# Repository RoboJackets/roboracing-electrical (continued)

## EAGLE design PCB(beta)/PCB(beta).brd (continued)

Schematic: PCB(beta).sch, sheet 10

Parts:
C82: 47pF; 0603
C83: 1.0uF; 0603
C87, C88: 0.1uF; 0603
C89: 10uF; 0603
FB4, FB5: 120Ω/1.3A; 0603
J9: DM3AT-SF-PEJM5
R88, R89, R91: 0; 0603
R90: 100k; 0603
U$27: IP4856CX25; 25-WLCSP
U$34: LXES15AAA1-100_ESD_SUPPRESSOR; 0402

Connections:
+1.8V: FB5.1; also elsewhere on the board
+3V3: FB4.1; also elsewhere on the board
+V1P8V_MICROSD: C87.1, FB5.2, U$27.B3 (VCCA)
+V3P3V_MICROSD: C88.1, C89.1, FB4.2, J9.4 (VCC), U$27.A4 (VSUPPLY), U$27.C4 (VSD_REF), U$34.1
+VLDO_SDCARD: C83.1, U$27.B4 (VLDO)
CHS_GND: U$34.2; also elsewhere on the board
GND: C82.2, C83.2, C87.2, C88.2, C89.2, J9.6 (GND), J9.B, J9.MOUNT0 (GND), J9.MOUNT1 (GND), J9.MOUNT2 (GND), J9.MOUNT3 (GND), R90.1, U$27.C3 (GND); also elsewhere on the board
SDCARD_CD_N: R89.1; also elsewhere on the board
SDCARD_CD_N_CONN: J9.A, R89.2, U$27.D3 (CD)
SDCARD_CLK: U$27.C1 (CLK_IN); also elsewhere on the board
SDCARD_CLK_CONN: C82.1, J9.5 (CLK), R91.2
SDCARD_CLK_CONN_R: R91.1, U$27.C5 (CLK_SD)
SDCARD_CMD: U$27.D2 (CMD_H); also elsewhere on the board
SDCARD_CMD_CONN: J9.3 (CMD/MOSI), U$27.D4 (CMD_SD)
SDCARD_D0: U$27.D1 (DATA0_H); also elsewhere on the board
SDCARD_D0_CONN: J9.7 (DATA0/MISO), U$27.D5 (DATA0_SD)
SDCARD_D1: U$27.E1 (DATA1_H); also elsewhere on the board
SDCARD_D1_CONN: J9.8 (DATA1/RSV), U$27.E5 (DATA1_SD)
SDCARD_D2: U$27.A1 (DATA2_H); also elsewhere on the board
SDCARD_D2_CONN: J9.1 (DATA2/NC), U$27.A5 (DATA2_SD)
SDCARD_D3: U$27.B1 (DATA3_H); also elsewhere on the board
SDCARD_D3_CONN: J9.2 (DATA3-CD/CS_N), U$27.B5 (DATA3_SD)
SDCARD_LVL_CLK_FB: U$27.E2 (CLK_FB); also elsewhere on the board
SDCARD_LVL_CMD_DIR: U$27.A2 (DIR_CMD); also elsewhere on the board
SDCARD_LVL_DAT_DIR: U$27.A3 (DIR_0), U$27.E3 (DIR_1_3)
SDCARD_LVL_SEL: U$27.B2 (SEL); also elsewhere on the board
SDCARD_PWR_DOWN_N: R88.1, R90.2; also elsewhere on the board
SDCARD_PWR_DOWN_N_R: R88.2, U$27.C2 (ENABLE)

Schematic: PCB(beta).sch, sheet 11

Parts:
C31, C32, C33, C34, C35, C36, C37, C38, C100, C101, C102: 0.1uF; 0603
C103, C104: 1.0uF; 0603
R92: 1.1k; 0603
R93, R109, R110, R111, R112, R113, R114, R115, R119, R120: 10k; 0603
R94: 100k; 0603
R116: 4.99k; 0603
R117, R118: 2.7k; 0603
U$28: SSM3K56CTL3FCT-ND_NCHAN_MOSFET; 3-XFDFN
U$54: PS8203TQFN32GTR-A3; TQFN32

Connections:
+1.8V: C102.1, C104.1, R92.2, R93.2, R117.2, R118.2, U$54.30 (VDDIO); also elsewhere on the board
+3V3: C101.1, C103.1, R109.2, R110.2, R113.2, R114.2, R119.2, U$54.11 (VDD); also elsewhere on the board
DCIN_EN: R109.1, R111.2, U$54.8 (DCIN_EN)
DDI1_CTRL_CLK: R118.1, U$54.31 (SCL_SRC); also elsewhere on the board
DDI1_CTRL_DAT: R117.1, U$54.32 (SDA_SRC); also elsewhere on the board
EQ: R110.1, R112.2, U$54.13 (EQ)
GND: C100.2, C101.2, C102.2, C103.2, C104.2, R94.1, R111.1, R112.1, R115.1, R120.1, U$28.P$2 (S), U$54.14 (GND), U$54.EXP (EPAD); also elsewhere on the board
HDMI_CEXT: C100.1, U$54.17 (CEXT)
HDMI_CLK_C_DN: C32.2, U$54.10 (IN_CKN)
HDMI_CLK_C_DP: C31.2, U$54.9 (IN_CKP)
HDMI_CLK_DN: C32.1; also elsewhere on the board
HDMI_CLK_DP: C31.1; also elsewhere on the board
HDMI_OB_CLK_DN: U$54.18 (OUT_CKN); also elsewhere on the board
HDMI_OB_CLK_DP: U$54.19 (OUT_CKP); also elsewhere on the board
HDMI_OB_DAT0_DN: U$54.21 (OUT_D0N); also elsewhere on the board
HDMI_OB_DAT0_DP: U$54.22 (OUT_D0P)
HDMI_OB_DAT1_DN: U$54.23 (OUT_D1N); also elsewhere on the board
HDMI_OB_DAT1_DP: U$54.24 (OUT_D1P); also elsewhere on the board
HDMI_OB_DAT2_DN: U$54.26 (OUT_D2N); also elsewhere on the board
HDMI_OB_DAT2_DP: U$54.27 (OUT_D2P); also elsewhere on the board
HDMI_OB_HPD_INV: U$54.25 (HPD_SNK)
HDMI_OB_SCL: U$54.28 (SCL_SNK); also elsewhere on the board
HDMI_OB_SDA: U$54.29 (SDA_SNK); also elsewhere on the board
HDMI_PRE: R119.1, R120.2, U$54.15 (PRE)
HDMI_REXT: R116.2, U$54.16 (REXT)
HDMI_TX_0_C_DN: C34.2, U$54.7 (IN_D0N)
HDMI_TX_0_C_DP: C33.2, U$54.6 (IN_D0P)
HDMI_TX_0_DN: C34.1; also elsewhere on the board
HDMI_TX_0_DP: C33.1; also elsewhere on the board
HDMI_TX_1_C_DN: C37.2, U$54.5 (IN_D1N)
HDMI_TX_1_C_DP: C35.2, U$54.4 (IN_D1P)
HDMI_TX_1_DN: C37.1; also elsewhere on the board
HDMI_TX_1_DP: C35.1; also elsewhere on the board
HDMI_TX_2_C_DN: C38.2, U$54.2 (IN_D2N)
HDMI_TX_2_C_DP: C36.2, U$54.1 (IN_D2P)
HDMI_TX_2_DN: C38.1; also elsewhere on the board
HDMI_TX_2_DP: C36.1; also elsewhere on the board
HPD_SRC: R92.1, U$28.P$3 (D); also elsewhere on the board
HPD_SRC_N: R93.1, R94.2, U$28.P$1 (G), U$54.3 (HPD_SRC)
LS_CFG: R114.1, R115.2, U$54.20 (CFG)
LS_PD_N: R113.1, U$54.12 (PD*)

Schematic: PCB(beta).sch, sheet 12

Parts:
C39, C40: 0.1uF; 0603
C41, C42: 0.22uF; 0603
D4, D5, D6: 0.5A/40V/420mV; SOD-323
J5: 685119134923
R22, R23: 2.7k; 0603
U$12, U$13, U$14, U$15: TCE0806G-900-2P-T200; 0302_(0806_METRIC)

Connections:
+5V: C39.1, D4.A, D5.A, D6.A; also elsewhere on the board
+V5P0V_D: C40.1, C41.1, C42.1, D6.C, J5.18 (+5VPOWER)
CHS_GND: U$12.P5_1 (5), U$12.P5_2 (5), U$12.P6_1 (6), U$12.P6_2 (6), U$13.P5_1 (5), U$13.P5_2 (5), U$13.P6_1 (6), U$13.P6_2 (6), U$14.P5_1 (5), U$14.P5_2 (5), U$14.P6_1 (6), U$14.P6_2 (6), U$15.P5_1 (5), U$15.P5_2 (5), U$15.P6_1 (6), U$15.P6_2 (6); also elsewhere on the board
GND: C39.2, C40.2, C41.2, C42.2, J5.2 (TMDSDATA2SHIELD), J5.5 (TMDSDATA1SHIELD), J5.8 (TMDSDATA0SHIELD), J5.11 (TMDSCLOCKSHIELD); also elsewhere on the board
HDMI_CLK_CONN_DN: J5.12 (TMDSCLOCK-), U$13.P2_1 (2), U$13.P2_2 (2), U$13.P2_3 (2)
HDMI_CLK_CONN_DP: J5.10 (TMDSCLOCK+), U$13.P1_1 (1), U$13.P1_2 (1), U$13.P1_3 (1)
HDMI_DAT0_CONN_DN: J5.9 (TMDSDATA0-), U$12.P2_1 (2), U$12.P2_2 (2), U$12.P2_3 (2)
HDMI_DAT0_CONN_DP: J5.7 (TMDSDATA0+), U$12.P1_1 (1), U$12.P1_2 (1), U$12.P1_3 (1)
HDMI_DAT1_CONN_DN: J5.6 (TMDSDATA1-), U$14.P2_1 (2), U$14.P2_2 (2), U$14.P2_3 (2)
HDMI_DAT1_CONN_DP: J5.4 (TMDSDATA1+), U$14.P1_1 (1), U$14.P1_2 (1), U$14.P1_3 (1)
HDMI_DAT2_CONN_DN: J5.3 (TMDSDATA2-), U$15.P2_1 (2), U$15.P2_2 (2), U$15.P2_3 (2)
HDMI_DAT2_CONN_DP: J5.1 (TMDSDATA2+), U$15.P1_1 (1), U$15.P1_2 (1), U$15.P1_3 (1)
HDMI_OB_CLK_DN: U$13.P3_1 (3), U$13.P3_2 (3), U$13.P3_3 (3); also elsewhere on the board
HDMI_OB_CLK_DP: U$13.P4_1 (4), U$13.P4_2 (4), U$13.P4_3 (4); also elsewhere on the board
HDMI_OB_DAT0_DN: U$12.P3_1 (3), U$12.P3_2 (3), U$12.P3_3 (3); also elsewhere on the board
HDMI_OB_DAT1_DN: U$14.P3_1 (3), U$14.P3_2 (3), U$14.P3_3 (3); also elsewhere on the board
HDMI_OB_DAT1_DP: U$14.P4_1 (4), U$14.P4_2 (4), U$14.P4_3 (4); also elsewhere on the board
HDMI_OB_DAT2_DN: U$15.P3_1 (3), U$15.P3_2 (3), U$15.P3_3 (3); also elsewhere on the board
HDMI_OB_DAT2_DP: U$15.P4_1 (4), U$15.P4_2 (4), U$15.P4_3 (4); also elsewhere on the board
HDMI_OB_SCL: J5.15 (SCL), R22.2; also elsewhere on the board
HDMI_OB_SCL_D: D4.C, R22.1
HDMI_OB_SDA: J5.16 (SDA), R23.2; also elsewhere on the board
HDMI_OB_SDA_D: D5.C, R23.1
TP_HDMI_CEC: J5.13 (CEC)

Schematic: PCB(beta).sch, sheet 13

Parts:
C43, C44, C45, C46, C47, C48, C49, C50, C51, C52: 0.1uF; 0603
R24, R29, R30, R39: 200k; 0603
R25, R26, R27, R28, R31, R32, R33, R34, R35, R36, R37, R38: 100k; 0603
U4, U5, U6, U7, U8: LSF0108RKSR; RKS20_1P1X3P1

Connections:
+1.8V: C44.1, C45.1, C47.1, C49.1, C51.1, R25.2, R26.2, R33.2, R34.2, R35.2, R36.2, U4.2 (VREF_A), U5.2 (VREF_A), U6.2 (VREF_A), U7.2 (VREF_A), U8.2 (VREF_A); also elsewhere on the board
+3V3: C50.1, R24.2, R27.2, R28.2, R29.2, R30.2, R31.2, R32.2, R37.2, R38.2, R39.2, U7.19 (VREF_B), U7.20 (EN); also elsewhere on the board
CLK_19P2M: U7.6 (A4); also elsewhere on the board
CLK_19P2M_LS: U7.15 (B4); also elsewhere on the board
CODEC_MCLK: U6.8 (A6); also elsewhere on the board
CODEC_MCLK_LS: U6.13 (B6); also elsewhere on the board
EN6: C52.1, R39.1, U8.19 (VREF_B), U8.20 (EN)
GND: C43.2, C44.2, C45.2, C46.2, C47.2, C48.2, C49.2, C50.2, C51.2, C52.2, U4.1 (GND), U4.21 (EPAD), U5.1 (GND), U5.21 (EPAD), U6.1 (GND), U6.21 (EPAD), U7.1 (GND), U7.21 (EPAD), U8.1 (GND), U8.21 (EPAD); also elsewhere on the board
GPIO_22: U7.3 (A1); also elsewhere on the board
GPIO_22_LS: U7.18 (B1); also elsewhere on the board
I2C_0_SCL: R34.1, U7.8 (A6); also elsewhere on the board
I2C_0_SCL_LS: R31.1, U7.13 (B6); also elsewhere on the board
I2C_0_SDA: R33.1, U7.4 (A2); also elsewhere on the board
I2C_0_SDA_LS: R32.1, U7.17 (B2); also elsewhere on the board
I2S_1_CLK: U6.9 (A7); also elsewhere on the board
I2S_1_CLK_LS: U6.12 (B7); also elsewhere on the board
I2S_1_FS: U6.7 (A5); also elsewhere on the board
I2S_1_FS_LS: U6.14 (B5); also elsewhere on the board
I2S_1_RXD: U6.6 (A4); also elsewhere on the board
I2S_1_RXD_LS: U6.15 (B4); also elsewhere on the board
I2S_1_TXD: U6.5 (A3); also elsewhere on the board
I2S_1_TXD_LS: U6.16 (B3); also elsewhere on the board
ISH_GPIO_0: U8.6 (A4); also elsewhere on the board
ISH_GPIO_0_LS: U8.15 (B4); also elsewhere on the board
ISH_GPIO_1: U8.5 (A3); also elsewhere on the board
ISH_GPIO_1_LS: U8.16 (B3); also elsewhere on the board
ISH_GPIO_2: U4.8 (A6); also elsewhere on the board
ISH_GPIO_2_LS: U4.13 (B6); also elsewhere on the board
ISH_GPIO_3: U4.7 (A5); also elsewhere on the board
ISH_GPIO_3_LS: U4.14 (B5); also elsewhere on the board
ISH_GPIO_4: U8.4 (A2); also elsewhere on the board
ISH_GPIO_4_LS: U8.17 (B2); also elsewhere on the board
ISH_GPIO_5: U4.6 (A4); also elsewhere on the board
ISH_GPIO_5_LS: U4.15 (B4); also elsewhere on the board
ISH_GPIO_6: U8.3 (A1); also elsewhere on the board
ISH_GPIO_6_LS: U8.18 (B1); also elsewhere on the board
ISH_I2C_0_SCL: R25.1, U5.6 (A4); also elsewhere on the board
ISH_I2C_0_SCL_LS: R27.1, U5.15 (B4); also elsewhere on the board
ISH_I2C_0_SDA: R26.1, U5.5 (A3); also elsewhere on the board
ISH_I2C_0_SDA_LS: R28.1, U5.16 (B3); also elsewhere on the board
ISH_I2C_1_SCL: R36.1, U8.8 (A6); also elsewhere on the board
ISH_I2C_1_SCL_LS: R37.1, U8.13 (B6); also elsewhere on the board
ISH_I2C_1_SDA: R35.1, U8.7 (A5); also elsewhere on the board
ISH_I2C_1_SDA_LS: R38.1, U8.14 (B5); also elsewhere on the board
unnamed: C48.1, R30.1, U6.19 (VREF_B), U6.20 (EN)
unnamed: C46.1, R29.1, U5.19 (VREF_B), U5.20 (EN)
unnamed: C43.1, R24.1, U4.19 (VREF_B), U4.20 (EN)
PMIC_PWRGOOD: U6.10 (A8); also elsewhere on the board
PMIC_PWRGOOD_LS: U6.11 (B8); also elsewhere on the board
PMIC_RESET_N: U4.3 (A1); also elsewhere on the board
PMIC_RESET_N_LS: U4.18 (B1); also elsewhere on the board
PWM_0: U4.5 (A3); also elsewhere on the board
PWM_0_LS: U4.16 (B3); also elsewhere on the board
PWM_1: U4.4 (A2); also elsewhere on the board
PWM_1_LS: U4.17 (B2); also elsewhere on the board
PWM_2: U5.4 (A2); also elsewhere on the board
PWM_2_LS: U5.17 (B2); also elsewhere on the board
PWM_3: U5.3 (A1); also elsewhere on the board
PWM_3_LS: U5.18 (B1); also elsewhere on the board
SPI_1_CLK: U6.3 (A1); also elsewhere on the board
SPI_1_CLK_LS: U6.18 (B1); also elsewhere on the board
SPI_1_FS0: U7.10 (A8); also elsewhere on the board
SPI_1_FS0_LS: U7.11 (B8); also elsewhere on the board
SPI_1_FS2: U5.7 (A5); also elsewhere on the board
SPI_1_FS2_LS: U5.14 (B5); also elsewhere on the board
SPI_1_MISO: U7.7 (A5); also elsewhere on the board
SPI_1_MISO_LS: U7.14 (B5); also elsewhere on the board
SPI_1_MOSI: U6.4 (A2); also elsewhere on the board
SPI_1_MOSI_LS: U6.17 (B2); also elsewhere on the board
UART_0_TXD: U7.5 (A3); also elsewhere on the board
UART_0_TXD_LS: U7.16 (B3); also elsewhere on the board
UART_1_RXD: U4.10 (A8); also elsewhere on the board
UART_1_RXD_LS: U4.11 (B8); also elsewhere on the board
UART_1_TXD: U4.9 (A7); also elsewhere on the board
UART_1_TXD_LS: U4.12 (B7); also elsewhere on the board

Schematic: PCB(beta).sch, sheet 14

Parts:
C53, C54, C55, C56: 0.1uF; 0603
D7, D8, D9, D10: GREEN; LED-0603
J6: SSM-120-S-DV; CON40_2X20_DU_SSM
Q1, Q2: TRANS_NPN_DUAL-MBT3904DW1T1; SC70-6
R40, R41, R42, R43: 1.1k; 0603
R44, R45, R46, R47: 560; 2010
U$35, U$36: LXES15AAA1-100_ESD_SUPPRESSOR; 0402

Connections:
+5V: R44.2, R45.2, R46.2, R47.2; also elsewhere on the board
+VDD1: C55.1, C56.1, J6.34, U$35.1; also elsewhere on the board
+VDD3: C53.1, C54.1, J6.40, U$36.1; also elsewhere on the board
CLK_19P2M_LS: J6.5; also elsewhere on the board
CODEC_MCLK_LS: J6.20; also elsewhere on the board
GND: C53.2, C54.2, C55.2, C56.2, J6.36, J6.37, J6.38, J6.39, Q1.1 (E), Q1.4 (E), Q2.1 (E), Q2.4 (E), U$35.2, U$36.2; also elsewhere on the board
GPIO_22_LS: J6.1; also elsewhere on the board
I2C_0_SCL_LS: J6.13; also elsewhere on the board
I2C_0_SDA_LS: J6.11; also elsewhere on the board
I2S_1_CLK_LS: J6.18; also elsewhere on the board
I2S_1_FS_LS: J6.16; also elsewhere on the board
I2S_1_RXD_LS: J6.12; also elsewhere on the board
I2S_1_TXD_LS: J6.14; also elsewhere on the board
ISH_GPIO0_COL: D7.A, R44.1
ISH_GPIO0_COL_D: D7.C, Q1.3 (C)
ISH_GPIO1_COL: D8.A, R45.1
ISH_GPIO1_COL_D: D8.C, Q1.6 (C)
ISH_GPIO2_COL: D9.A, R46.1
ISH_GPIO2_COL_D: D9.C, Q2.3 (C)
ISH_GPIO3_COL: D10.A, R47.1
ISH_GPIO3_COL_D: D10.C, Q2.6 (C)
ISH_GPIO_0: R40.1; also elsewhere on the board
ISH_GPIO_0_LS: J6.35; also elsewhere on the board
ISH_GPIO_0_R: Q1.5 (B), R40.2
ISH_GPIO_1: R41.1; also elsewhere on the board
ISH_GPIO_1_LS: J6.33; also elsewhere on the board
ISH_GPIO_1_R: Q1.2 (B), R41.2
ISH_GPIO_2: R42.1; also elsewhere on the board
ISH_GPIO_2_LS: J6.31; also elsewhere on the board
ISH_GPIO_2_R: Q2.5 (B), R42.2
ISH_GPIO_3: R43.1; also elsewhere on the board
ISH_GPIO_3_LS: J6.29; also elsewhere on the board
ISH_GPIO_3_R: Q2.2 (B), R43.2
ISH_GPIO_4_LS: J6.27; also elsewhere on the board
ISH_GPIO_5_LS: J6.25; also elsewhere on the board
ISH_GPIO_6_LS: J6.23; also elsewhere on the board
ISH_I2C_0_SCL_LS: J6.17; also elsewhere on the board
ISH_I2C_0_SDA_LS: J6.15; also elsewhere on the board
ISH_I2C_1_SCL_LS: J6.21; also elsewhere on the board
ISH_I2C_1_SDA_LS: J6.19; also elsewhere on the board
PMIC_PWRGOOD_LS: J6.9; also elsewhere on the board
PMIC_RESET_N_LS: J6.3; also elsewhere on the board
PWM_0_LS: J6.26; also elsewhere on the board
PWM_1_LS: J6.28; also elsewhere on the board
PWM_2_LS: J6.30; also elsewhere on the board
PWM_3_LS: J6.32; also elsewhere on the board
SPI_1_CLK_LS: J6.10; also elsewhere on the board
SPI_1_FS0_LS: J6.6; also elsewhere on the board
SPI_1_FS2_LS: J6.8; also elsewhere on the board
SPI_1_MISO_LS: J6.2; also elsewhere on the board
SPI_1_MOSI_LS: J6.4; also elsewhere on the board
UART_0_TXD_LS: J6.7; also elsewhere on the board
UART_1_RXD_LS: J6.24; also elsewhere on the board
UART_1_TXD_LS: J6.22; also elsewhere on the board

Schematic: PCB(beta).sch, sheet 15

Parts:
C57, C58, C59, C60, C61, C62, C63, C64, C65, C66, C67, C68, C69, C70: 0.1uF; 0603
J7: SSM-120-S-DV; CON40_2X20_DU_SSM
R48, R49, R50, R51, R52, R53, R58, R59: 100k; 0603
R54, R55, R56, R57: 200k; 0603
U9, U10, U11, U12: LSF0108RKSR; RKS20_1P1X3P1
U$37, U$38, U$39: LXES15AAA1-100_ESD_SUPPRESSOR; 0402

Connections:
+1.8V: C57.1, C59.1, C61.1, C63.1, C65.1, C66.1, J7.12, R48.2, R49.2, R50.2, R58.2, U9.2 (VREF_A), U10.2 (VREF_A), U11.2 (VREF_A), U12.2 (VREF_A), U$37.1; also elsewhere on the board
+3V3: C67.1, C68.1, J7.6, J7.8, R51.2, R52.2, R53.2, R54.2, R55.2, R56.2, R57.2, R59.2, U$38.1; also elsewhere on the board
+5V: C69.1, C70.1, J7.2, J7.4, U$39.1; also elsewhere on the board
AVS_M_CLK_A1: U10.3 (A1); also elsewhere on the board
AVS_M_CLK_A1_LS: J7.26, U10.18 (B1)
AVS_M_CLK_B1: U10.8 (A6); also elsewhere on the board
AVS_M_CLK_B1_LS: J7.24, U10.13 (B6)
AVS_M_DATA_1: U10.9 (A7); also elsewhere on the board
AVS_M_DATA_1_LS: J7.22, U10.12 (B7)
BLDRW_0_PWM: U10.5 (A3); also elsewhere on the board
BLDRW_0_PWM_LS: J7.17, U10.16 (B3)
DISPLAY_0_BIAS_EN: U10.4 (A2); also elsewhere on the board
DISPLAY_0_BIAS_EN_LS: J7.13, U10.17 (B2)
DISPLAY_0_BKLT_EN: U10.6 (A4); also elsewhere on the board
DISPLAY_0_BKLT_EN_LS: J7.15, U10.15 (B4)
DISPLAY_0_RST_N: U10.10 (A8); also elsewhere on the board
DISPLAY_0_RST_N_LS: J7.11, U10.11 (B8)
FLASH_RST_N: U11.4 (A2); also elsewhere on the board
FLASH_RST_N_LS: J7.18, U11.17 (B2)
FLASH_TORCH: U11.5 (A3); also elsewhere on the board
FLASH_TORCH_LS: J7.16, U11.16 (B3)
FLASH_TRIGGER: U11.3 (A1); also elsewhere on the board
FLASH_TRIGGER_LS: J7.20, U11.18 (B1)
GND: C57.2, C58.2, C59.2, C60.2, C61.2, C62.2, C63.2, C64.2, C65.2, C66.2, C67.2, C68.2, C69.2, C70.2, J7.1, J7.3, J7.5, J7.7, J7.9, J7.14, U9.1 (GND), U9.21 (EPAD), U10.1 (GND), U10.21 (EPAD), U11.1 (GND), U11.21 (EPAD), U12.1 (GND), U12.21 (EPAD), U$37.2, U$38.2, U$39.2; also elsewhere on the board
I2C_1_SCL: R48.1, U9.10 (A8); also elsewhere on the board
I2C_1_SCL_LS: J7.33
I2C_1_SDA: R58.1, U12.3 (A1); also elsewhere on the board
I2C_1_SDA_LS: J7.31, R59.1, U12.18 (B1)
I2C_2_SCL: R49.1, U9.8 (A6); also elsewhere on the board
I2C_2_SCL_LS: J7.37, R51.1, U9.13 (B6)
I2C_2_SDA: R50.1, U9.9 (A7); also elsewhere on the board
I2C_2_SDA_LS: J7.35, R52.1, R53.1, U9.11 (B8), U9.12 (B7)
ISH_UART_0_CTS: U9.4 (A2); also elsewhere on the board
ISH_UART_0_CTS_LS: J7.40, U9.17 (B2)
ISH_UART_0_RTS: U9.5 (A3); also elsewhere on the board
ISH_UART_0_RTS_LS: J7.38, U9.16 (B3)
ISH_UART_0_RXD: U9.6 (A4); also elsewhere on the board
ISH_UART_0_RXD_LS: J7.36, U9.15 (B4)
ISH_UART_0_TXD: U9.7 (A5); also elsewhere on the board
ISH_UART_0_TXD_LS: J7.34, U9.14 (B5)
unnamed: C62.1, R56.1, U11.19 (VREF_B), U11.20 (EN)
unnamed: C60.1, R55.1, U10.19 (VREF_B), U10.20 (EN)
unnamed: C64.1, R57.1, U12.19 (VREF_B), U12.20 (EN)
unnamed: C58.1, R54.1, U9.19 (VREF_B), U9.20 (EN)
PMIC_SLPCLK_1: U9.3 (A1); also elsewhere on the board
PMIC_SLPCLK_1_LS: U9.18 (B1)
PMIC_SPLCLK_1_LS: J7.39
SPI_0_CLK: U12.10 (A8); also elsewhere on the board
SPI_0_CLK_LS: J7.25, U12.11 (B8)
SPI_0_FS0: U11.6 (A4); also elsewhere on the board
SPI_0_FS0_LS: J7.19, U11.15 (B4)
SPI_0_FS1: U10.7 (A5); also elsewhere on the board
SPI_0_FS1_LS: J7.21, U10.14 (B5)
SPI_0_FS2: U12.7 (A5); also elsewhere on the board
SPI_0_FS2_LS: J7.23, U12.14 (B5)
SPI_0_MISO: U12.5 (A3); also elsewhere on the board
SPI_0_MISO_LS: J7.29, U12.16 (B3)
SPI_0_MOSI: U12.9 (A7); also elsewhere on the board
SPI_0_MOSI_LS: J7.27, U12.12 (B7)
UART_0_CTS: U12.4 (A2); also elsewhere on the board
UART_0_CTS_LS: J7.32, U12.17 (B2)
UART_0_RTS: U12.8 (A6); also elsewhere on the board
UART_0_RTS_LS: J7.30, U12.13 (B6)
UART_0_RXD: U12.6 (A4); also elsewhere on the board
UART_0_RXD_LS: J7.28, U12.15 (B4); also elsewhere on the board

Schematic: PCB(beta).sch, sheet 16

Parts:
R60: 100k; 0603
R61: 100; 0603
R62, R63: 3.3k; 0603
S1, S2, S3: MOMENTARY-SWITCH-SPST-2-SMD-4.6X2.8MM; TACTILE_SWITCH_SMD_4.6X2.8MM
U$16: TSM-102-01-L-DV-TR; 4X-.145X.05_SQ
U$40, U$41, U$42, U$43, U$44: LXES15AAA1-100_ESD_SUPPRESSOR; 0402

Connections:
+VDD1: R60.2, R61.2; also elsewhere on the board
BTN_N: R60.1, S2.3, S2.4, U$41.1; also elsewhere on the board
GND: R62.1, R63.1, S1.1, S1.2, S2.1, S2.2, U$40.2, U$41.2, U$42.2, U$43.2, U$44.2; also elsewhere on the board
PMIC_PWRBTN_N: S1.3, S1.4, U$42.1; also elsewhere on the board
SPI_1_FS2: U$16.P$3, U$44.1; also elsewhere on the board
SPI_1_FS2_PD: R62.2, U$16.P$4
UART_1_TXD: U$16.P$1, U$43.1; also elsewhere on the board
UART_1_TXD_PD: R63.2, U$16.P$2
UART_2_TXD: S3.1, S3.2, U$40.1; also elsewhere on the board
UART_2_TXD_PU: R61.1, S3.3, S3.4

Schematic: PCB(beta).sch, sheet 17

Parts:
C71, C90: 0.1uF; 0603
H1, H2, H3, H4: MOUNT-PAD-ROUND4.1; 4,1-PAD
J8: CONN_03SMD; 1X03-1MM-RA
R64, R65, R66, R67, R96: 10k; 0603
R68, R69, R70, R71, R72, R73, R74: 0; 0603
R95: 1.1k; 0603
U$17: M24M02-DRMN6TP; SOIC8
U$29: LXES15AAA1-100_ESD_SUPPRESSOR; 0402
U$30: BK-916-TR_12MM_COINCELL; 12MM_COINCELL
U$45, U$46, U$47, U$48: 92320A282_1/8_SPACER; 1/8"RING

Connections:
+3V3: R96.2; also elsewhere on the board
+5V: C90.1, J8.1; also elsewhere on the board
+VDD1: C71.1, R64.2, R66.2, R69.2; also elsewhere on the board
+VRTC: R95.1; also elsewhere on the board
CHS_GND: R71.2, R72.2, R73.2, R74.2; also elsewhere on the board
EEPROM_E2: R66.1, R67.2, U$17.3 (E2)
EEPROM_VCC: R69.1, U$17.8 (VCC)
EEPROM_WC_N: R64.1, R65.2, U$17.7 (/WC)
FAN_CTRL: J8.2, R96.1
GND: C71.2, C90.2, H1.B4,1, H2.B4,1, H3.B4,1, H4.B4,1, J8.3, R65.1, R67.1, R71.1, R72.1, R73.1, R74.1, U$17.4 (VSS), U$29.2, U$30.P$3 (-), U$45.P$1, U$46.P$1, U$47.P$1, U$48.P$1; also elsewhere on the board
I2C_0_SCL: R70.1; also elsewhere on the board
I2C_0_SCL_EE_R: R70.2, U$17.6 (SCL)
I2C_0_SDA: R68.2; also elsewhere on the board
I2C_0_SDA_EE_R: R68.1, U$17.5 (SDA)
unnamed: R95.2, U$29.1, U$30.P$1 (+), U$30.P$2 (+)

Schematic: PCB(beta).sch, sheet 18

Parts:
C130, C131: 22pF; 0603
C132, C133: 0.1uF; 0603
J10: CONN_03X2FEMALE_SMD; 2X3_SMD
Q3, Q4: 220mA/50V/3.5Ω; SOT23-3
R121, R122, R123, R124, R125: 10k; 0603
S4: MOMENTARY-SWITCH-SPST-2-SMD-4.6X2.8MM; TACTILE_SWITCH_SMD_4.6X2.8MM
U13: ATMEGA328P_TQFP; TQFP32-08
Y1: 16MHz; CRYSTAL-SMD-5X3.2-4PAD

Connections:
+3V3: Q3.1 (G), Q4.1 (G), R122.2, R125.2; also elsewhere on the board
+5V: C133.1, J10.2, R121.2, R123.2, R124.2, U13.4 (VCC), U13.6 (VCC), U13.18 (AVCC); also elsewhere on the board
GND: C130.1, C131.1, C132.2, C133.2, J10.6, S4.1, S4.2, U13.3 (GND), U13.5 (GND), U13.21 (AGND); also elsewhere on the board
MICRO_RST: J10.5, R121.1, S4.3, S4.4, U13.29 (PC6(/RESET))
unnamed: J10.4, U13.15 (PB3(MOSI/OC2))
unnamed: J10.1, U13.16 (PB4(MISO))
unnamed: J10.3, U13.17 (PB5(SCK))
unnamed: C130.2, U13.7 (PB6(XTAL1/TOSC1)), Y1.3 (2)
unnamed: C131.2, U13.8 (PB7(XTAL2/TOSC2)), Y1.1
unnamed: Q3.3 (D), R123.1, U13.30 (PD0(RXD))
unnamed: C132.1, U13.20 (AREF)
unnamed: Q4.3 (D), R124.1, U13.31 (PD1(TXD))
UART_0_RXD_LS: Q4.2 (S), R125.1; also elsewhere on the board
UART_0_TXD_LS: Q3.2 (S), R122.1; also elsewhere on the board

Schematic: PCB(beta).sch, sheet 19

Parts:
C134, C135: 18pF; 0603
C136: 1.0uF; 0603
C137, C138, C140, C141, C142, C143, C144, C145, C146, C147, C148, C149, C150, C151, C152, C153, C154, C157, C158, C159, C160, C161, C162, C163, C164, C169, C170, C171, C172, C176, C177, C180, C181, C182, C184: 0.1uF; 0603
C139, C155, C156: 10uF; 0603
C165, C166, C167, C168: 1nF; 0603
C173, C175: 4.7uF; 0603
C174: 10nF; 0603
C178, C179, C183, C185: 150uF; CPOL-RADIAL-2.5MM-6.5MM
FB6, FB7, FB8, FB9, FB10: 30Ω/1.8A; 0603
K2, K3, K4, K5: 692112030100
R126, R138, R139, R140, R141: 1M; 0603
R127, R128, R130, R132, R134, R135, R136, R137: 4.7k; 0603
R129: 9.53k; 0603
R131, R143, R144, R146, R147: 10k; 0603
R133: 90.9k; 0603
R142, R145: 25.5k; 0603
U$57: TUSB8041; QFN64-9X9
U$58: ADP1706ARDZ-1.1-R7; SOIC8
U$59, U$60: TPS2561DRCT; 10-VSON
Y2: 24MHz; CRYSTAL-SMD-5X3.2-4PAD

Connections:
+1V1: C148.1, C149.1, C150.1, C151.1, C152.1, C153.1, C154.1, C155.1, C175.1, U$57.5 (VDD1), U$57.8 (VDD2), U$57.13 (VDD3), U$57.21 (VDD4), U$57.28 (VDD5), U$57.31 (VDD6), U$57.51 (VDD7), U$57.57 (VDD8), U$58.5 (OUT), U$58.6 (OUT2), U$58.7 (SENSE)
+3V3: C173.1, FB6.2, R134.2, R135.2, R136.2, R137.2, R143.2, R144.2, R146.2, R147.2, U$58.1 (EN), U$58.3 (IN), U$58.4 (IN2); also elsewhere on the board
+3V3_HUB: C156.1, C157.1, C158.1, C159.1, C160.1, FB6.1
+5V: C176.1, C177.1, U$59.2_1 (IN), U$59.2_2 (IN), U$59.3_1 (IN2), U$59.3_2 (IN2), U$60.2_1 (IN), U$60.2_2 (IN), U$60.3_1 (IN2), U$60.3_2 (IN2); also elsewhere on the board
DN1_VBUS: C178.1 (+), C180.1, FB7.1, U$59.9_1 (OUT1), U$59.9_2 (OUT1)
DN2_VBUS: C179.1 (+), C181.1, FB8.1, U$59.8_1 (OUT2), U$59.8_2 (OUT2)
DN3_VBUS: C182.1, C183.1 (+), FB9.1, U$60.9_1 (OUT1), U$60.9_2 (OUT1)
DN4_VBUS: FB10.1
GND: C134.1, C135.1, C136.2, C139.2, C156.2, C157.2, C158.2, C159.2, C160.2, C161.2, C162.2, C163.2, C164.2, C165.1, C165.2, C166.1, C166.2, C167.1, C167.2, C168.1, C168.2, C169.1, C169.2, C170.1, C170.2, C171.1, C171.2, C172.1, C172.2, C173.2, C174.2, C175.2, C176.2, C177.2, C178.2 (-), C179.2 (-), C180.2, C181.2, C182.2, C183.2 (-), C184.2, C185.2 (-), K2.4 (GND), K2.7 (GND_DRAIN), K3.4 (GND), K3.7 (GND_DRAIN), K4.4 (GND), K5.4 (GND), R127.1, R128.1, R129.1, R130.1, R131.1, R132.1, R138.1, R138.2, R139.1, R139.2, R140.1, R140.2, R141.1, R141.2, R142.1, R145.1, U$57.16 (VDD33_1), U$57.34 (VDD33_2), U$57.52 (VDD33_3), U$57.63 (VDD33_4), U$57.EXP (PAD), U$58.2 (GND), U$59.1_1 (GND), U$59.1_2 (GND), U$59.PAD1 (PAD), U$59.PAD2 (PAD), U$59.PAD3 (PAD), U$60.1_1 (GND), U$60.1_2 (GND), U$60.PAD1 (PAD), U$60.PAD2 (PAD), U$60.PAD3 (PAD); also elsewhere on the board
GRST#: C136.1, U$57.50 (GRST#)
ILIM1: R142.2, U$59.7_1 (ILIM), U$59.7_2 (ILIM)
ILIM2: R145.2, U$60.7_1 (ILIM), U$60.7_2 (ILIM)
unnamed: R127.2, U$57.49 (TEST)
unnamed: R129.2, U$57.64 (USB_R1)
unnamed: R132.2, U$57.45 (AUTOEN_HS_SUSPD)
unnamed: R128.2, U$57.42 (GANGED/SMBA2/HS_UP)
unnamed: R130.2, U$57.40 (FPMGT/SMBA1/SS_UP)
unnamed: R131.2, R133.2, U$57.48 (USB_VBUS)
unnamed: C140.1, U$57.27 (USB_SSTXM_DN4)
unnamed: C141.1, U$57.26 (USB_SSTXP_DN4)
unnamed: C142.1, U$57.20 (USB_SSTXM_DN3)
unnamed: C143.1, U$57.19 (USB_SSTXP_DN3)
unnamed: C144.1, U$57.12 (USB_SSTXM_DN2)
unnamed: C145.1, U$57.11 (USB_SSTXP_DN2)
unnamed: C147.1, U$57.4 (USB_SSTXM_DN1)
unnamed: C146.1, U$57.3 (USB_SSTXP_DN1)
unnamed: C148.2, C149.2, C150.2, C151.2, C152.2, C153.2, C154.2, C155.2
unnamed: C161.1, FB7.2, K2.1 (VBUS)
unnamed: C174.1, U$58.8 (SS)
unnamed: C162.1, FB8.2
unnamed: C163.1, FB9.2, K4.1 (VBUS)
unnamed: C184.1, C185.1 (+), U$60.8_1 (OUT2), U$60.8_2 (OUT2)
unnamed: C164.1, FB10.2, K5.1 (VBUS)
OVERCUR1Z: R143.1, U$57.46 (OVERCURZ1), U$59.10_1 (FAULT1Z), U$59.10_2 (FAULT1Z)
OVERCUR2Z: R144.1, U$57.47 (OVERCURZ2), U$59.6_1 (FAULT2Z), U$59.6_2 (FAULT2Z)
OVERCUR3Z: R146.1, U$57.44 (OVERCURZ3), U$60.10_1 (FAULT1Z), U$60.10_2 (FAULT1Z)
OVERCUR4Z: R147.1, U$57.43 (OVERCURZ4), U$60.6_1 (FAULT2Z), U$60.6_2 (FAULT2Z)
PWRCTL1_BATEN1: R134.1, U$57.36 (PWRCTL1/BATEN1), U$59.4_1 (EN1), U$59.4_2 (EN1)
PWRCTL2_BATEN2: R135.1, U$57.35 (PWRCTL2/BATEN2), U$59.5_1 (EN2), U$59.5_2 (EN2)
PWRCTL3_BATEN3: R136.1, U$57.33 (PWRCTL3/BATEN3), U$60.4_1 (EN1), U$60.4_2 (EN1)
PWRCTL4_BATEN4: R137.1, U$57.32 (PWRCTL4/BATEN4), U$60.5_1 (EN2), U$60.5_2 (EN2)
USBA_USB2_1_DN: U$57.54 (USB_DM_UP); also elsewhere on the board
USBA_USB2_1_DP: U$57.53 (USB_DP_UP); also elsewhere on the board
USBA_USB3_1_RX_DN: U$57.59 (USB_SSRXM_UP); also elsewhere on the board
USBA_USB3_1_RX_DP: U$57.58 (USB_SSRXP_UP); also elsewhere on the board
USBA_USB3_1_TX_DN: C138.1; also elsewhere on the board
USBA_USB3_1_TX_DP: C137.1; also elsewhere on the board
USB_DM_DN1: K2.2 (D-), U$57.2 (USB_DM_DN1)
USB_DM_DN2: K3.2 (D-), U$57.10 (USB_DM_DN2)
USB_DM_DN3: K4.2 (D-), U$57.18 (USB_DM_DN3)
USB_DM_DN4: K5.2 (D-), U$57.25 (USB_DM_DN4)
USB_DP_DN1: K2.3 (D+), U$57.1 (USB_DP_DN1)
USB_DP_DN2: K3.3 (D+), U$57.9 (USB_DP_DN2)
USB_DP_DN3: K4.3 (D+), U$57.17 (USB_DP_DN3)
USB_DP_DN4: K5.3 (D+), U$57.24 (USB_DP_DN4)
USB_SSRXM_DN1: K2.5 (STDA_SSRX-), U$57.7 (USB_SSRXM_DN1)
USB_SSRXM_DN2: K3.5 (STDA_SSRX-), U$57.15 (USB_SSRXM_DN2)
USB_SSRXM_DN3: K4.5 (STDA_SSRX-), U$57.23 (USB_SSRXM_DN3)
USB_SSRXM_DN4: K5.5 (STDA_SSRX-), U$57.30 (USB_SSRXM_DN4)
USB_SSRXP_DN1: K2.6 (STDA_SSRX+), U$57.6 (USB_SSRXP_DN1)
USB_SSRXP_DN2: K3.6 (STDA_SSRX+), U$57.14 (USB_SSRXP_DN2)
USB_SSRXP_DN3: K4.6 (STDA_SSRX+), U$57.22 (USB_SSRXP_DN3)
USB_SSRXP_DN4: K5.6 (STDA_SSRX+), U$57.29 (USB_SSRXP_DN4)
USB_SSTXM_DN1: C147.2, K2.8 (STDA_SSTX-)
USB_SSTXM_DN2: C144.2, K3.8 (STDA_SSTX-)
USB_SSTXM_DN3: C142.2, K4.8 (STDA_SSTX-)
USB_SSTXM_DN4: C140.2, K5.8 (STDA_SSTX-)
USB_SSTXP_DN1: C146.2, K2.9 (STDA_SSTX+)
USB_SSTXP_DN2: C145.2, K3.9 (STDA_SSTX+)
USB_SSTXP_DN3: C143.2, K4.9 (STDA_SSTX+)
USB_SSTXP_DN4: C141.2, K5.9 (STDA_SSTX+)
VBUS_HUB: C139.1, R133.1
X: C137.2, U$57.55 (USB_SSTXP_UP)
XI: C135.2, R126.2, U$57.62 (XI), Y2.3 (2)
XO: C134.2, R126.1, U$57.61 (XO), Y2.1
Y: C138.2, U$57.56 (USB_SSTXM_UP)

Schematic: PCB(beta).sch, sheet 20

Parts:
C81, C186: 0.1uF; 0603
U14: 433MHz; RFM69HCW-XXXS2
U15: SN74LVC1G373DCKR; SOT65P210X110-6N

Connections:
+3V3: C81.1, C186.1, U14.13 (3.3V), U15.5 (VCC); also elsewhere on the board
GND: C81.2, C186.2, U14.1 (GND), U14.8 (GND), U14.10 (GND), U15.2 (GND); also elsewhere on the board

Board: 2 copper layers, 466 parts (0 on the bottom side), 426 nets, no tracks yet.

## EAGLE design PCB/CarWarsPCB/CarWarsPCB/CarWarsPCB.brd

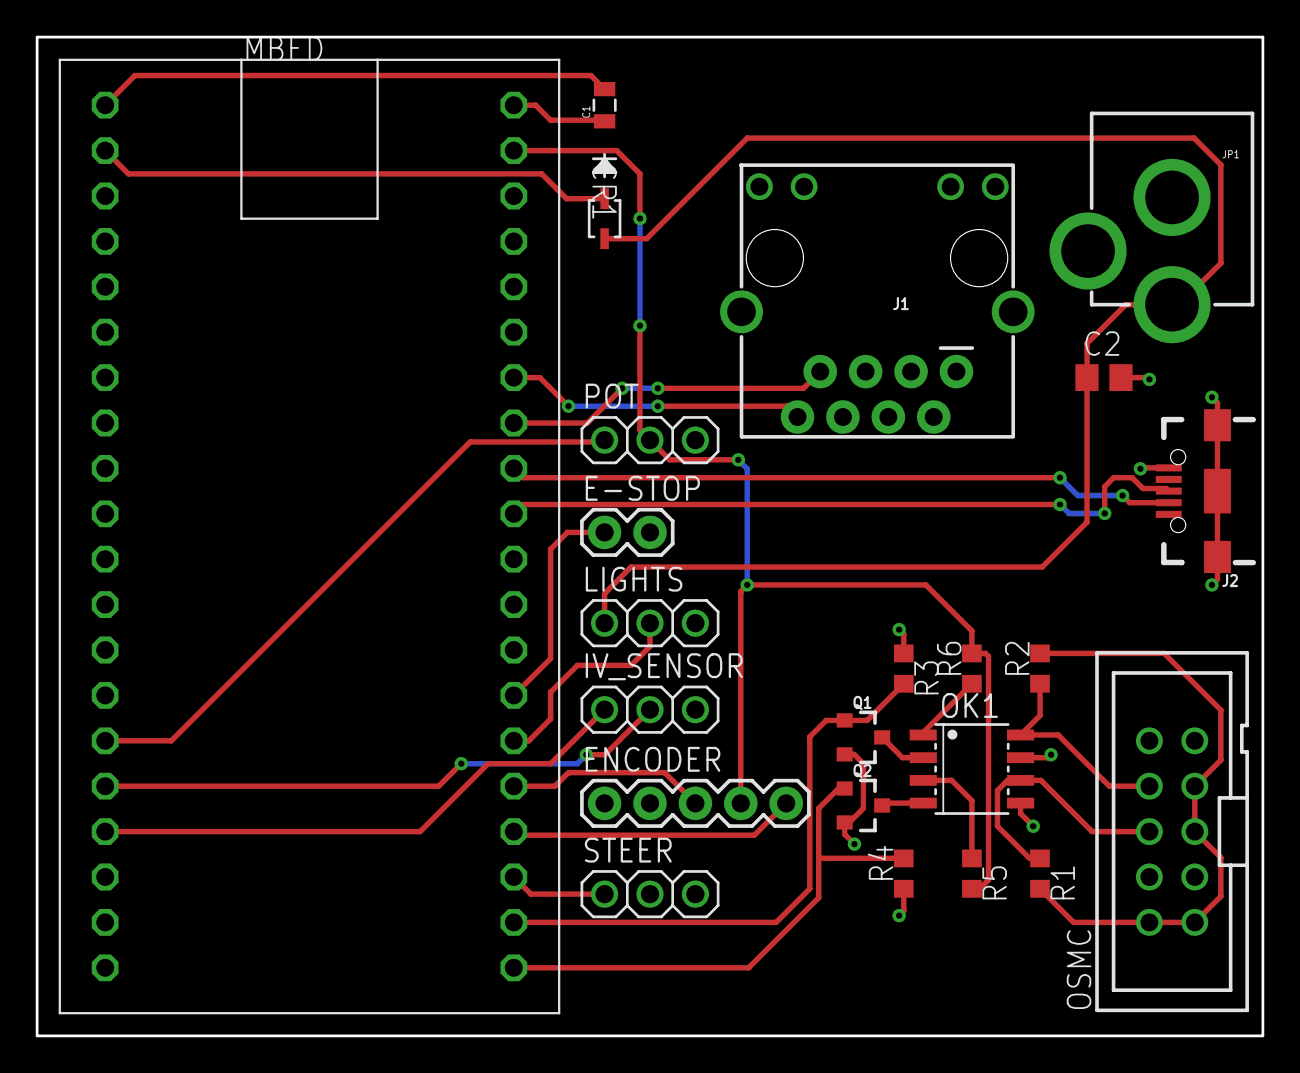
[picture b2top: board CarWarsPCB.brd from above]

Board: 2 copper layers, 68.6 x 55.9 mm, 23 parts (0 on the bottom side), 29 nets.

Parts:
C1: 0.1uF; 0805
C2: C0805
CR1: BAT60JFILM; SOD-323
E-STOP: 1X02
ENCODER: 1X05
IV_SENSOR: 1X03
J1: MAGJACK
J2: USB-B-MICRO-SMD
JP1: POWER_JACKPTH; POWER_JACK_PTH
LIGHTS: 1X03
MBED: MBED1768; DIL40_0.9
OK1: MOCD208M; SOIC08-FAIRCHILD
OSMC: 2510-; PAK100/2500-10
POT: 1X03
Q1, Q2: 220mA/50V/3.5Ω; SOT23-3
R1, R2, R3, R4: 10K; R0603
R5, R6: 62; R0603
STEER: 1X03

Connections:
+3V3: C1.1, J1.3, J1.6, MBED.40
+5V: ENCODER.4, MBED.39, POT.2, R5.2, R6.2
+12V: OSMC.1, OSMC.2, OSMC.5, OSMC.7, R1.2, R2.2
DGND: OK1.5, OK1.7, OSMC.4, OSMC.9, OSMC.10
DRIVE_DIR_3V3: MBED.22, Q1.1, R3.2
DRIVE_DIR_12V: OK1.8, OSMC.8, R2.1
DRIVE_PWM_3V3: MBED.21, Q2.1, R4.2
DRIVE_PWM_12V: OK1.6, OSMC.6, R1.1
E-STOP_STATUS: E-STOP.1, MBED.27
ENC_A: ENCODER.3, MBED.25
ENC_B: ENCODER.5, MBED.24
ETH_RD+: J1.1, MBED.35
ETH_RD-: J1.2, MBED.36
ETH_TD+: J1.7, MBED.33
ETH_TD-: J1.8, MBED.34
GND: C1.2, C2.2, E-STOP.2, ENCODER.1, IV_SENSOR.3, J1.M1, J1.M2, J2.GND, J2.SHIELD1, J2.SHIELD2, J2.SHIELD3, JP1.GND, JP1.GNDBREAK, LIGHTS.3, MBED.1, POT.3, Q1.2, Q2.2, R3.1, R4.1, STEER.3
I_SENSE: IV_SENSOR.1, MBED.17
unnamed: CR1.1, MBED.2
unnamed: OK1.2, Q1.3
unnamed: OK1.4, Q2.3
unnamed: OK1.3, R5.1
unnamed: OK1.1, R6.1
unnamed: J2.D-, MBED.32
unnamed: J2.D+, MBED.31
NEOPIXEL_CONTROL: LIGHTS.2, MBED.26
STEER_POT: MBED.15, POT.1
STEER_PWM: MBED.23, STEER.1
VCC: C2.1, CR1.2, JP1.PWR, LIGHTS.1
V_SENSE: IV_SENSOR.2, MBED.16
